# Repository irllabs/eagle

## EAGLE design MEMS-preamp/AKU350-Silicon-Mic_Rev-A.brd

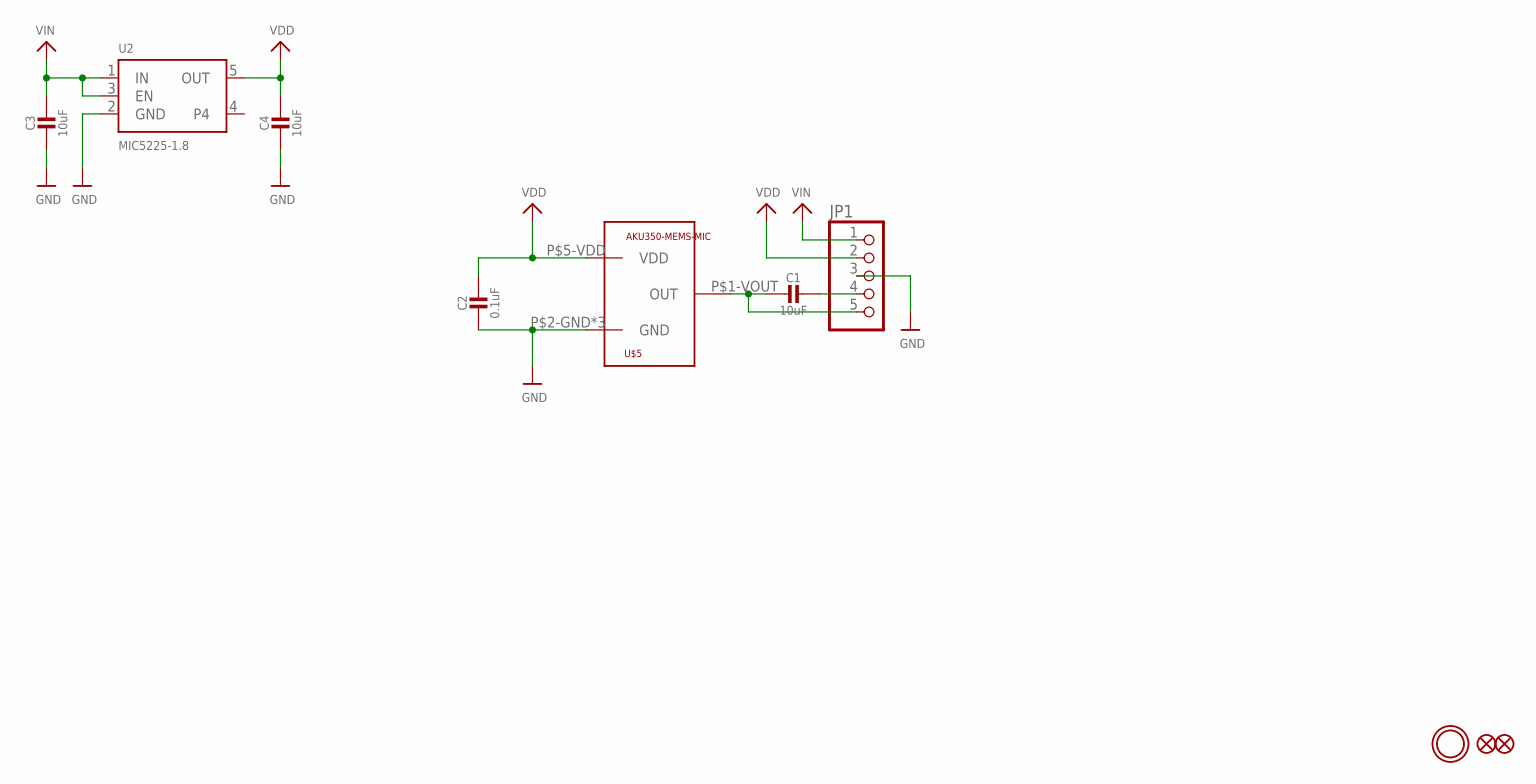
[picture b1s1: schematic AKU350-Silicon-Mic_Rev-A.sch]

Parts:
C1, C3, C4: 10uF; 0805-NO
C2: 0.1uF; 0805-NO
FID1, FID2: FIDUCIAL""; FIDUCIAL_1MM
JP1: HEADER-1X576MIL; 1X05_ROUND_76
U2: MIC5225-1.8; SOT23-5
U$5: AKU350-MEMS-MIC
U$12: MOUNTINGHOLE2.5; MOUNTINGHOLE_2.5_PLATED

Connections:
GND: C2.2, C3.2, C4.2, JP1.3, U2.2 (GND), U$5.P$2-GND (GND), U$5.P$3-GND (GND), U$5.P$4-GND (GND)
unnamed: C1.2, JP1.5, U$5.P$1-VOUT (OUT)
unnamed: C1.1, JP1.4
VDD: C2.1, C4.1, JP1.2, U2.5 (OUT), U$5.P$5-VDD (VDD)
VIN: C3.1, JP1.1, U2.1 (IN), U2.3 (EN)

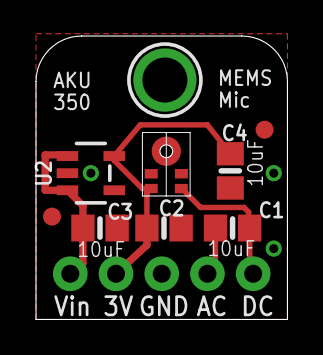
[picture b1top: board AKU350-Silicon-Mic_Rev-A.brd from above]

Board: 2 copper layers, 14.0 x 15.7 mm, 10 parts (0 on the bottom side), 5 nets.

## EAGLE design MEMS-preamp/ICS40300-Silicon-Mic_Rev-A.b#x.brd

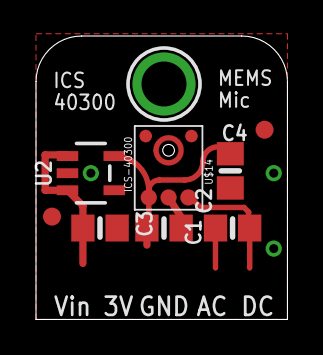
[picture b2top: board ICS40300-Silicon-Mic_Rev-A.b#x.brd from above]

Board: 2 copper layers, 14.0 x 15.7 mm, 10 parts (1 on the bottom side), 4 nets.

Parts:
C1, C3, C4: 10uF; 0805-NO
C2: 0.1uF; 0805-NO
FID1, FID2: FIDUCIAL""; FIDUCIAL_1MM
U2: MIC5225-3.3; SOT23-5
U$5: ADAFRUIT_3.5MM
U$12: MOUNTINGHOLE2.5; MOUNTINGHOLE_2.5_PLATED
U$14: ICS-40300

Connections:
GND: C2.2, C3.2, C4.2, U2.2, U$14.GND, U$14.GND1, U$14.GND2, U$14.GND3
unnamed: C1.2, U$14.OUT
VDD: C2.1, C4.1, U2.5, U$14.VDD
VIN: C3.1, U2.1, U2.3

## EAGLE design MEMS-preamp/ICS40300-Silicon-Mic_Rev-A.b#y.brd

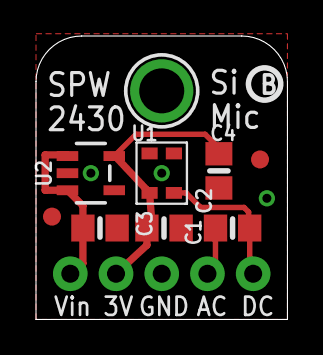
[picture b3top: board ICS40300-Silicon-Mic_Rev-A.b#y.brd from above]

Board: 2 copper layers, 14.0 x 15.7 mm, 12 parts (1 on the bottom side), 5 nets.

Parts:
C1, C3, C4: 10uF; 0805-NO
C2: 0.1uF; 0805-NO
FID1, FID2: FIDUCIAL""; FIDUCIAL_1MM
JP1: 1X05_ROUND_76
U1: SPW2430HR5H-B
U2: MIC5225-3.3; SOT23-5
U$5: ADAFRUIT_3.5MM
U$12: MOUNTINGHOLE2.5; MOUNTINGHOLE_2.5_PLATED
U$13: PCBFEAT-REV-040

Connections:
GND: C2.2, C3.2, C4.2, JP1.3, U1.2, U1.3, U2.2
unnamed: C1.2, JP1.5, U1.1
unnamed: C1.1, JP1.4
VDD: C2.1, C4.1, JP1.2, U1.4, U2.5
VIN: C3.1, JP1.1, U2.1, U2.3

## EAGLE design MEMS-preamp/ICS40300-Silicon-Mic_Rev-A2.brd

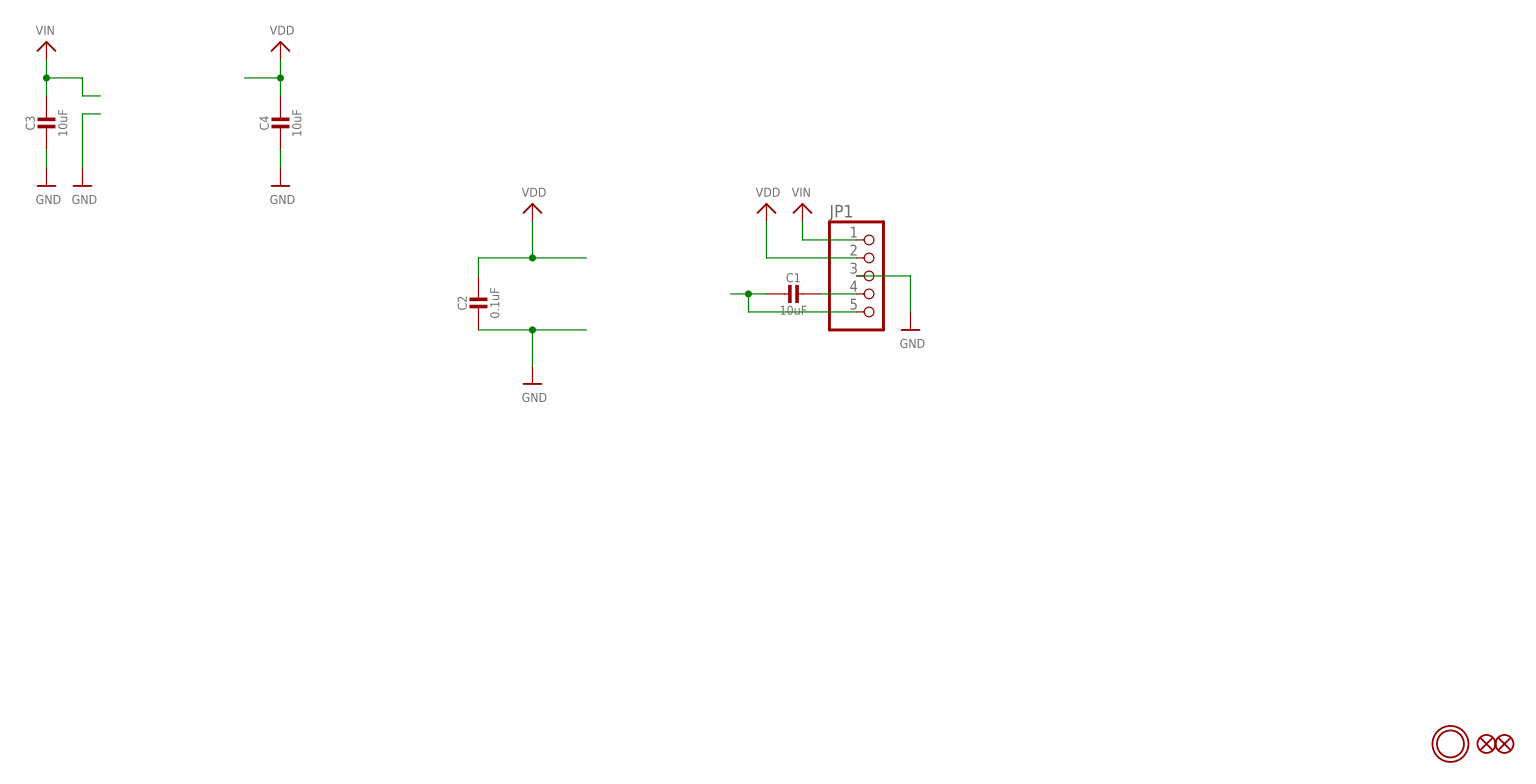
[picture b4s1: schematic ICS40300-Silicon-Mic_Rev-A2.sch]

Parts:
C1, C3, C4: 10uF; 0805-NO
C2: 0.1uF; 0805-NO
FID1, FID2: FIDUCIAL""; FIDUCIAL_1MM
JP1: HEADER-1X576MIL; 1X05_ROUND_76
U$12: MOUNTINGHOLE2.5; MOUNTINGHOLE_2.5_PLATED

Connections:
GND: C2.2, C3.2, C4.2, JP1.3
unnamed: C1.2, JP1.5
unnamed: C1.1, JP1.4
VDD: C2.1, C4.1, JP1.2
VIN: C3.1, JP1.1

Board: 2 copper layers, 8 parts (0 on the bottom side), 5 nets, no tracks yet.

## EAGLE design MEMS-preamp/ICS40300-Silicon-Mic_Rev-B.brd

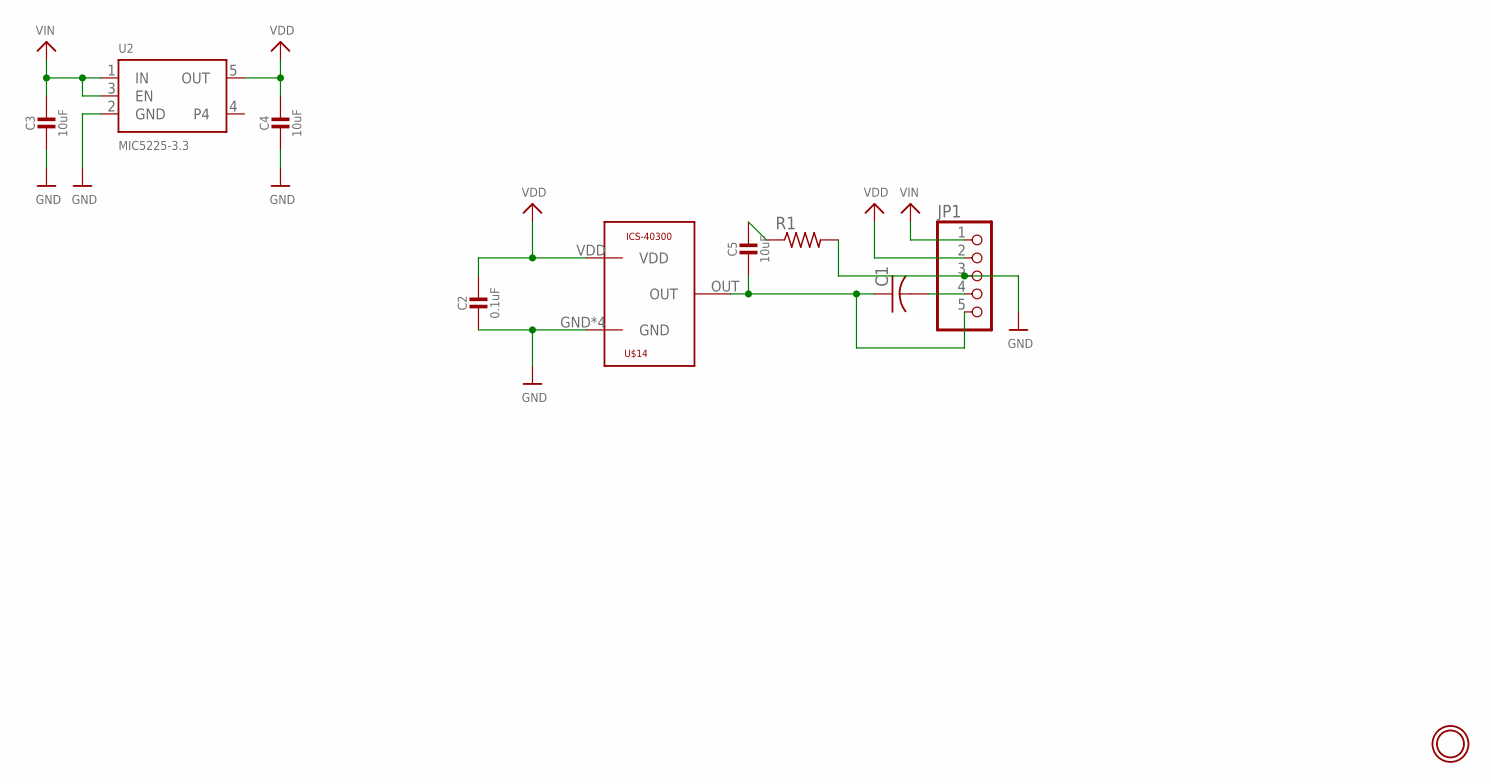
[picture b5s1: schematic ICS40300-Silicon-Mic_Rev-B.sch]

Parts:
C1: C-USC3216; C3216
C2: 0.1uF; 0805-NO
C3, C4, C5: 10uF; 0805-NO
JP1: HEADER-1X576MIL; 1X05_ROUND_76
R1: R-US_M0805; M0805
U2: MIC5225-3.3; SOT23-5
U$12: MOUNTINGHOLE2.5; MOUNTINGHOLE_2.5_PLATED
U$14: ICS-40300

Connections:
GND: C2.2, C3.2, C4.2, JP1.3, R1.2, U2.2 (GND), U$14.GND, U$14.GND1 (GND), U$14.GND2 (GND), U$14.GND3 (GND)
unnamed: C1.1, C5.2, JP1.5, U$14.OUT
unnamed: C1.2, JP1.4
unnamed: C5.1, R1.1
VDD: C2.1, C4.1, JP1.2, U2.5 (OUT), U$14.VDD
VIN: C3.1, JP1.1, U2.1 (IN), U2.3 (EN)

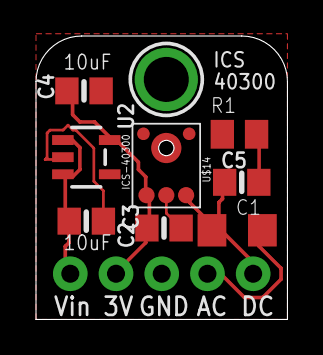
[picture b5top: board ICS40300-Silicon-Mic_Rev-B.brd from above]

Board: 2 copper layers, 14.0 x 15.7 mm, 10 parts (0 on the bottom side), 6 nets.

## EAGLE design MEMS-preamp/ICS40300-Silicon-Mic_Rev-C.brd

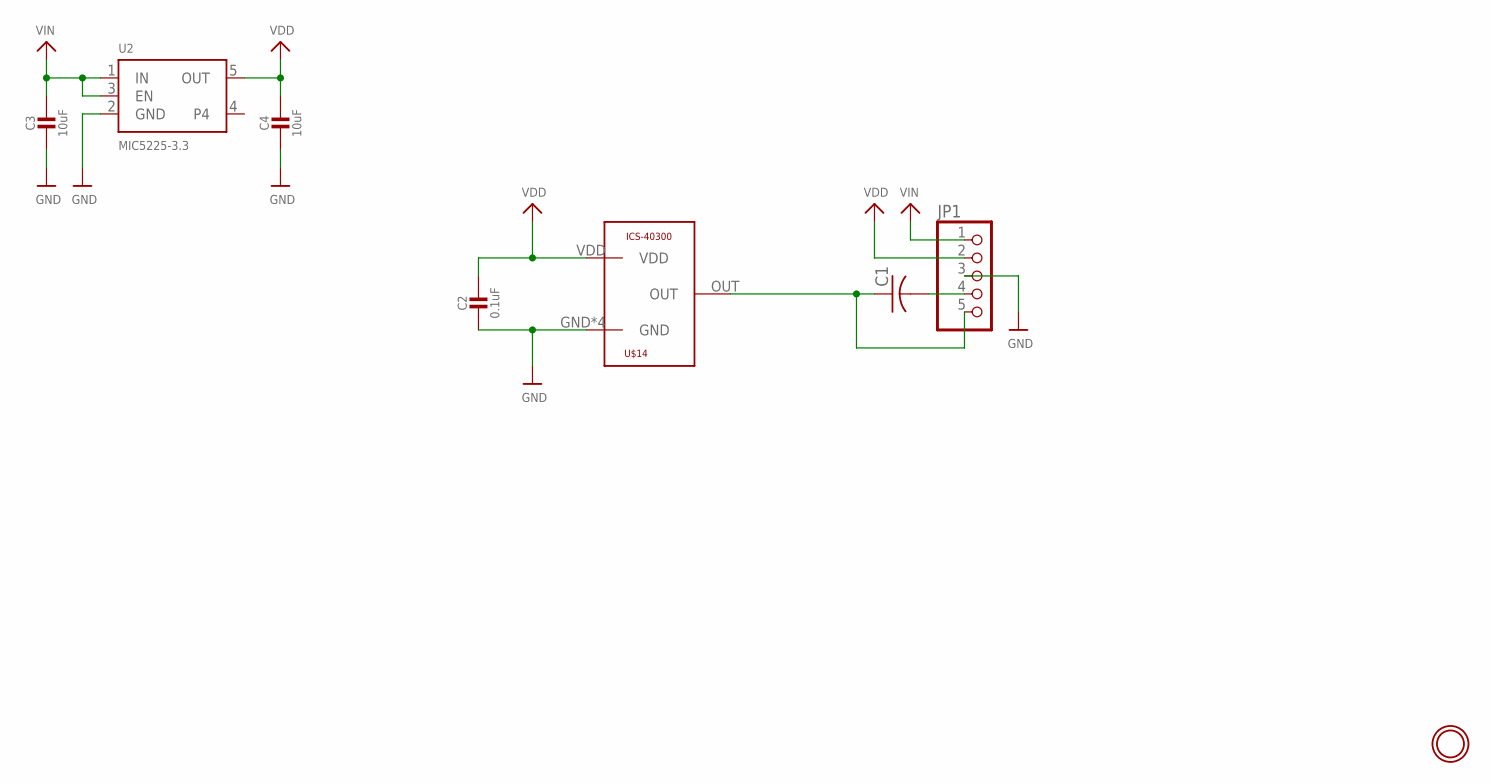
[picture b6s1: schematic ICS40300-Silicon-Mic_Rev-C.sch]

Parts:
C1: C-US; CT7343
C2: 0.1uF; 0805-NO
C3, C4: 10uF; 0805-NO
JP1: HEADER-1X576MIL; 1X05_ROUND_76
U2: MIC5225-3.3; SOT23-5
U$12: MOUNTINGHOLE2.5; MOUNTINGHOLE_2.5_PLATED
U$14: ICS-40300

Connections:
GND: C2.2, C3.2, C4.2, JP1.3, U2.2 (GND), U$14.GND, U$14.GND1 (GND), U$14.GND2 (GND), U$14.GND3 (GND)
unnamed: C1.+ (1), JP1.5, U$14.OUT
unnamed: C1.- (2), JP1.4
VDD: C2.1, C4.1, JP1.2, U2.5 (OUT), U$14.VDD
VIN: C3.1, JP1.1, U2.1 (IN), U2.3 (EN)

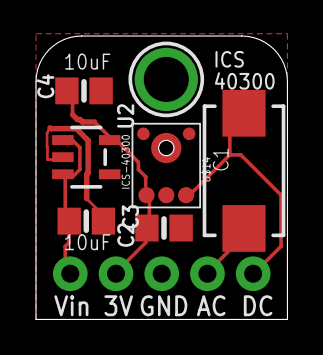
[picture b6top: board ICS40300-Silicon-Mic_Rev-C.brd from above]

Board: 2 copper layers, 14.0 x 15.7 mm, 8 parts (0 on the bottom side), 5 nets.

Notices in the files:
parts and their libraries:
microbuilder: This work is placed in the public domain, and may be freely used for commercial and non-commercial work with the following conditions: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
